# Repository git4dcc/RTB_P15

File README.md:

# RTB_P15

My homebrew P15 power board provides unmonitored power and is a stripped down version of the C11 power board. The main purpose of this card is to operate as a decoder tester/programmer via a USB connection to the PC. No external power supply is required as it can be powered via the USB and the optional isolated DC/DC converter.

<details>
<summary>See also</summary>

- [RTB_C10 - Master](/../../../../git4dcc/RTB_C10)
- [RTB_C11 - Power](/../../../../git4dcc/RTB_C11)
- [RTB_C12 - Booster](/../../../../git4dcc/RTB_C12)

</details>

<details>
<summary>User Guides</summary>

- User Guide - DE
- [User Guide - EN](https://rtb4dcc.de/rtb_user_guide_en/)

</details>

## Power Board features
- **passive**
  - no CPU on this board
- **DC/DC**
  - isolated DC/DC step up converter (5V->12V, 250mA)
  - (optional) external power connect (12V-16V, >1A)
- **Slots**
  - 1x Master slot
  - 1x Booster slot
  - 1x FDX extender (for development only)
- **Connectors**
  - terminal connector or (2.1mm / 2.5mm) barrel jack for external power
  - DCC connector

# Hardware
The PCB layout uses SMD footprints down to 0603 parts. Handsoldering is possible.
Further, the PCB has been optimized for automated assembly (BOM and Position files as CSV).

## PCB
- 2-layer PCB, FR4, 1.6mm
- CPU: none

# YouTube
See the (P15, C10, C12) used in the Decoder Tester use case.<br><br>

This project is intended for hobby use only and is distributed in accordance with the Apache License 2.0 agreement.

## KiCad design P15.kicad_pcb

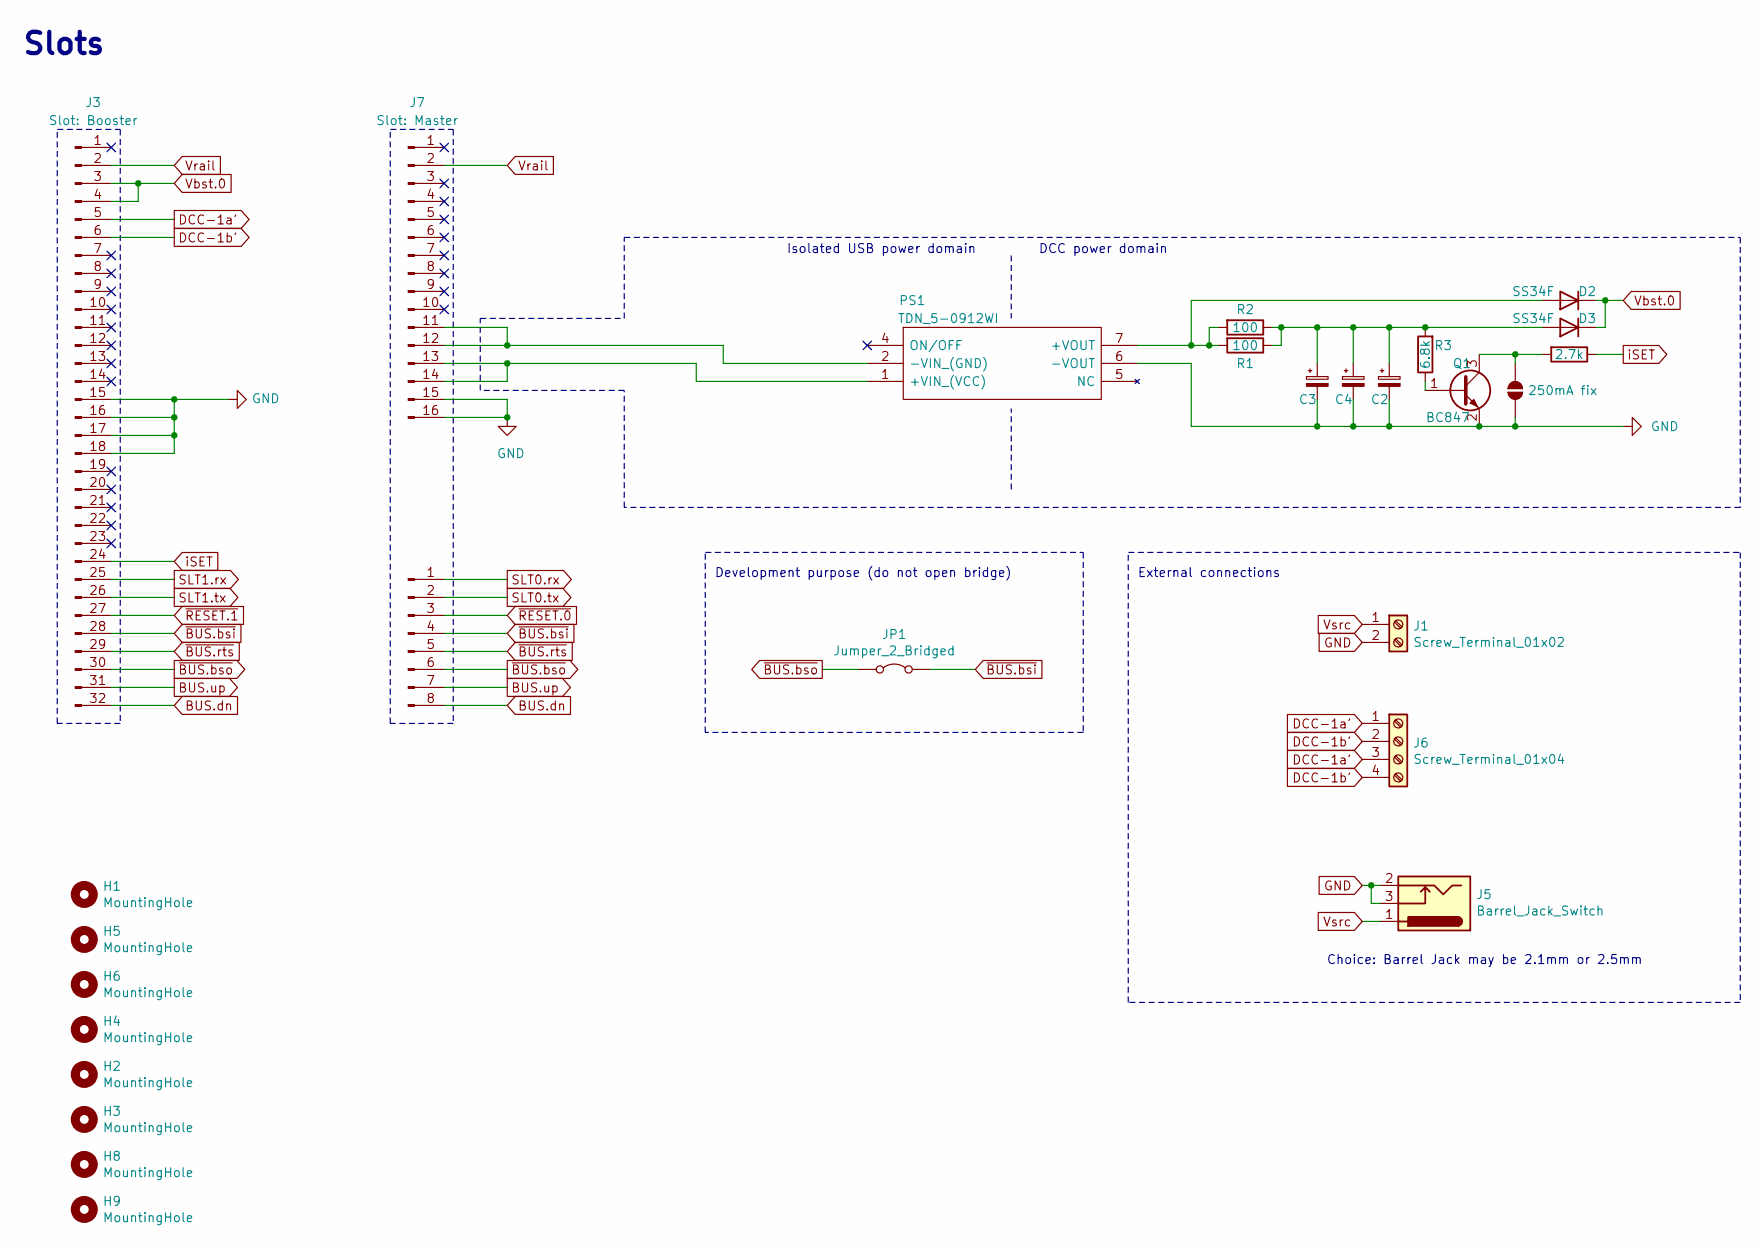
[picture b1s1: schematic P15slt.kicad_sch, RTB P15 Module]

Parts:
C2, C3, C4: 680u/20V; CP_Radial_D8.0mm_P3.50mm; Mouser 667-EEU-FR1E681L
D2, D3: SS34F; D_SOD-123F; LCSC Part # C60396
H1, H2, H3, H4, H5, H6, H8, H9: MountingHole; MountingHole_3.2mm_M3_ISO7380_Pad
J1: Screw_Terminal_01x02; 1725656
J3: Slot: Booster; PinSocket_1x32_P2.54mm_Vertical
J4: Slot-a1; PinSocket_1x08_P2.54mm_Vertical
J5: Barrel_Jack_Switch; BarrelJack_CLIFF_FC681465S_SMT_Horizontal; Mouser 163-0179-EX
J6: Screw_Terminal_01x04; 1725672
J7: Slot: Master; PinSocket_1x16_P2.54mm_Vertical
JP1: Jumper_2_Bridged; SolderJumper-2_P1.3mm_Bridged_RoundedPad1.0x1.5mm
JP2: 250mA fix; SolderJumper-2_P1.3mm_Open_Pad1.0x1.5mm
PS1: TDN_5-0912WI; TDN52412WI; Mouser 495-TDN5-0912WI
Q1: BC847; SOT-23; LCSC Part # C7420337
R1, R2: 100; R_1206_3216Metric; LCSC Part # C17901
R3: 6.8k; R_0603_1608Metric; LCSC Part # C23212
R4: 2.7k; R_0603_1608Metric; LCSC Part # C13167

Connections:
BUS.dn: J3.32, J4.8; also elsewhere on the board
BUS.up: J3.31, J4.7; also elsewhere on the board
DCC-1a': J3.5, J6.1, J6.3
DCC-1b': J3.6, J6.2, J6.4
GND: C2.2, C3.2, C4.2, J1.2, J3.15, J3.16, J3.17, J3.18, J5.2, J5.3, J7.15, J7.16, JP2.2 (B), PS1.6 (-VOUT), Q1.2 (E); also elsewhere on the board
unnamed: D2.2 (A), PS1.7 (+VOUT), R1.2, R2.2
unnamed: C2.1, C3.1, C4.1, D3.2 (A), R1.1, R2.1, R3.2
unnamed: J7.11, J7.12, PS1.2 (-VIN_(GND))
unnamed: J7.13, J7.14, PS1.1 (+VIN_(VCC))
unnamed: JP2.1 (A), Q1.3 (C), R4.2
unnamed: Q1.1 (B), R3.1
SLT0.rx: J4.1
SLT0.tx: J4.2
SLT1.rx: J3.25
SLT1.tx: J3.26
Vbst.0: D2.1 (K), D3.1 (K), J3.3, J3.4; also elsewhere on the board
Vrail: J3.2, J7.2; also elsewhere on the board
Vsrc: J1.1, J5.1; also elsewhere on the board
iSET: J3.24, R4.1
~BUS.bsi: J3.28, J4.4, JP1.2 (B); also elsewhere on the board
~BUS.bso: J3.30, J4.6, JP1.1 (A); also elsewhere on the board
~BUS.rts: J3.29, J4.5; also elsewhere on the board
~RESET.0: J4.3
~RESET.1: J3.27

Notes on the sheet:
Slots
Choice: Barrel Jack may be 2.1mm or 2.5mm
Isolated USB power domain
External connections
DCC power domain
Development purpose (do not open bridge)

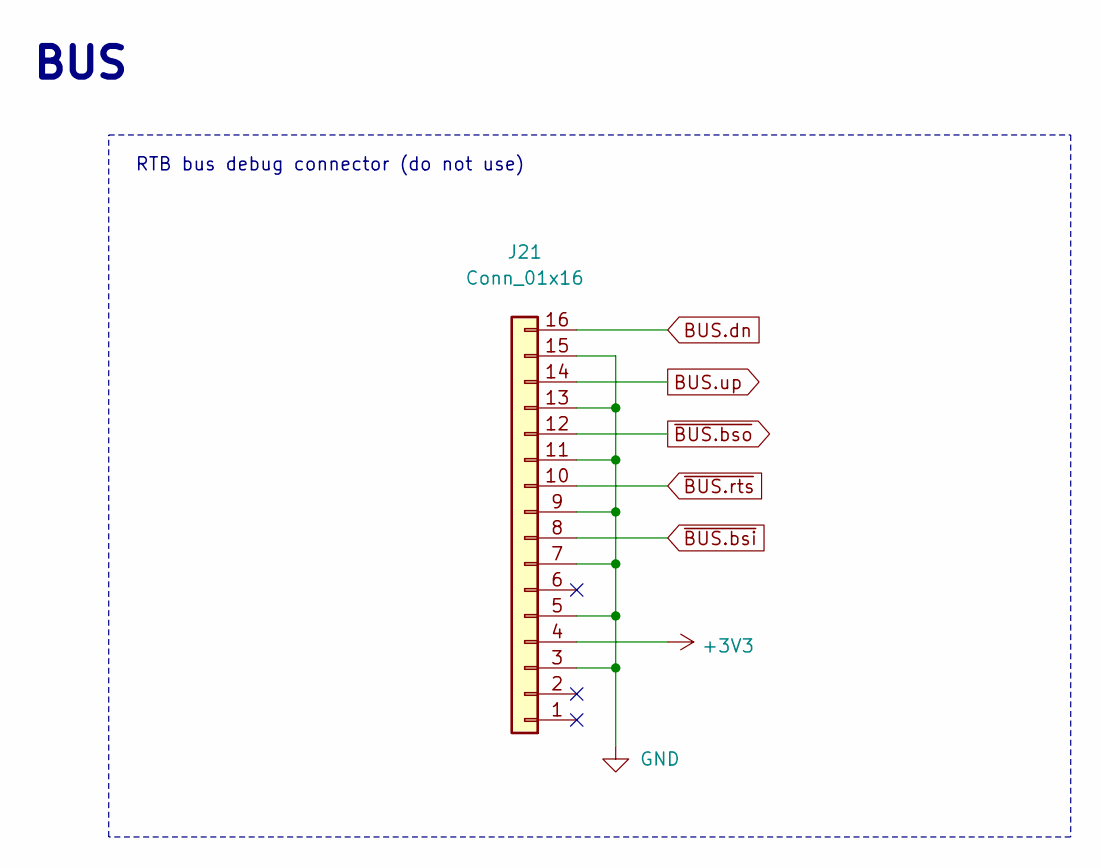
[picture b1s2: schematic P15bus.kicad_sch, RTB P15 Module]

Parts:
J21: Conn_01x16; PinHeader_2x08_P2.54mm_Vertical

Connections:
+3V3: J21.4
BUS.dn: J21.16; also elsewhere on the board
BUS.up: J21.14; also elsewhere on the board
GND: J21.3, J21.5, J21.7, J21.9, J21.11, J21.13, J21.15; also elsewhere on the board
~BUS.bsi: J21.8; also elsewhere on the board
~BUS.bso: J21.12; also elsewhere on the board
~BUS.rts: J21.10; also elsewhere on the board

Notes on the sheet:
RTB bus debug connector (do not use)
BUS

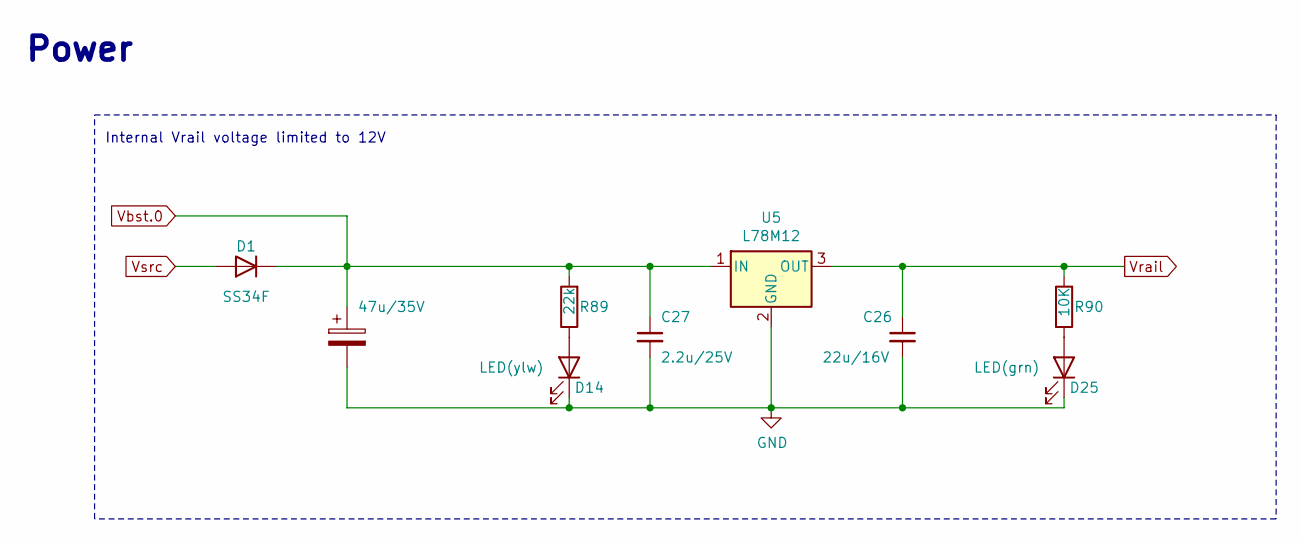
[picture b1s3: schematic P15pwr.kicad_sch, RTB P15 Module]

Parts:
C15: 47u/35V; CP_EIA-7343-43_Kemet-X; LCSC Part # C696814
C26: 22u/16V; C_1206_3216Metric; LCSC Part # C12891
C27: 2.2u/25V; C_1206_3216Metric; LCSC Part # C50254
D1: SS34F; D_SOD-123F; LCSC Part # C60396
D14: LED(ylw); LED_0603_1608Metric
D25: LED(grn); LED_0603_1608Metric
R89: 22k; R_0603_1608Metric; LCSC Part # C31850
R90: 10K; R_0603_1608Metric; LCSC Part # C25804
U5: L78M12; TO-252-2; LCSC Part # C22357875

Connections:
GND: C15.2, C26.2, C27.2, D14.1 (K), D25.1 (K), U5.2 (GND); also elsewhere on the board
unnamed: D14.2 (A), R89.1
unnamed: D25.2 (A), R90.1
Vbst.0: C15.1, C27.1, D1.1 (K), R89.2, U5.1 (IN); also elsewhere on the board
Vrail: C26.1, R90.2, U5.3 (OUT); also elsewhere on the board
Vsrc: D1.2 (A); also elsewhere on the board

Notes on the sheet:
Power
Internal Vrail voltage limited to 12V

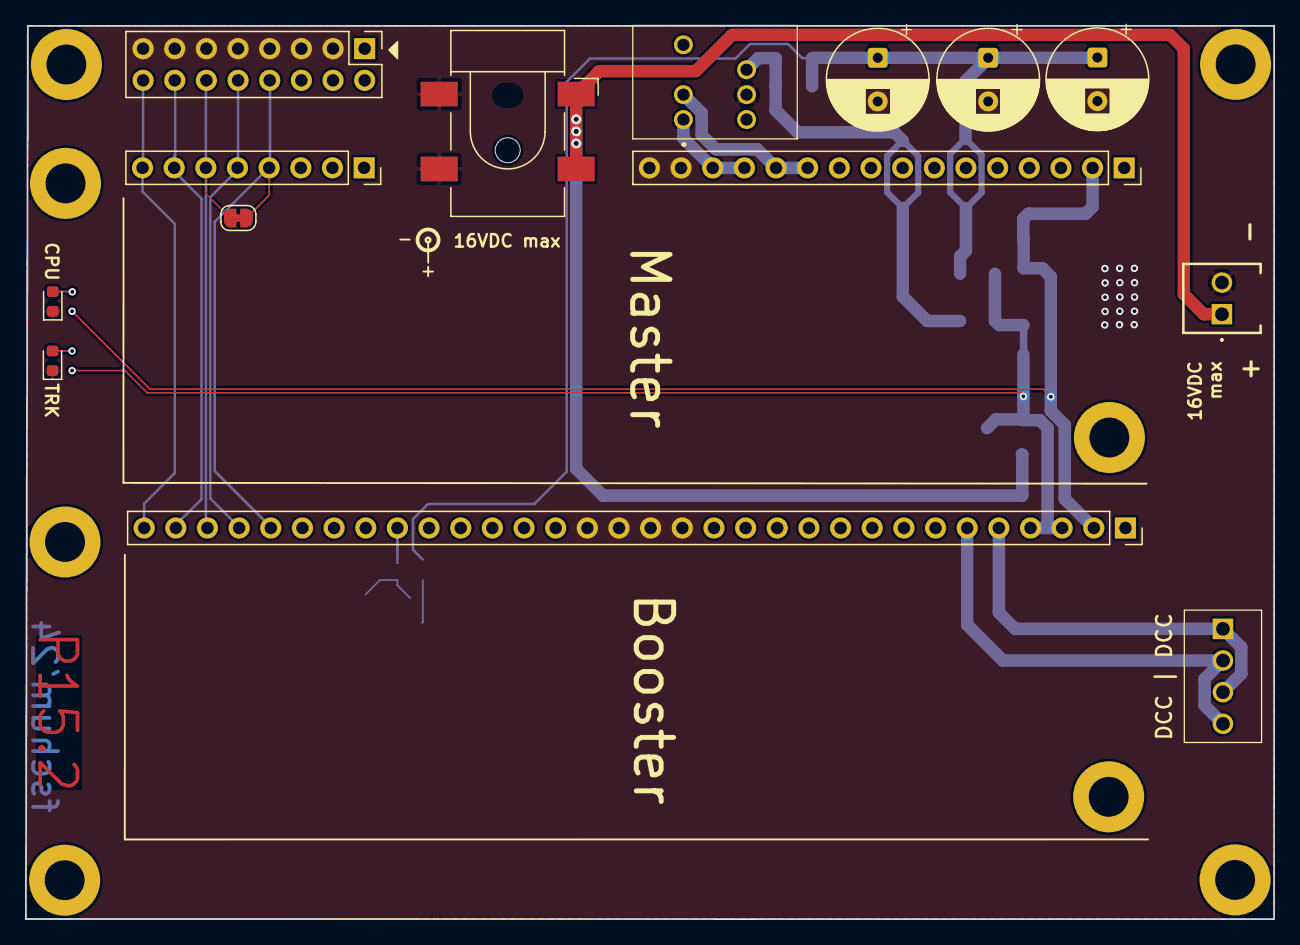
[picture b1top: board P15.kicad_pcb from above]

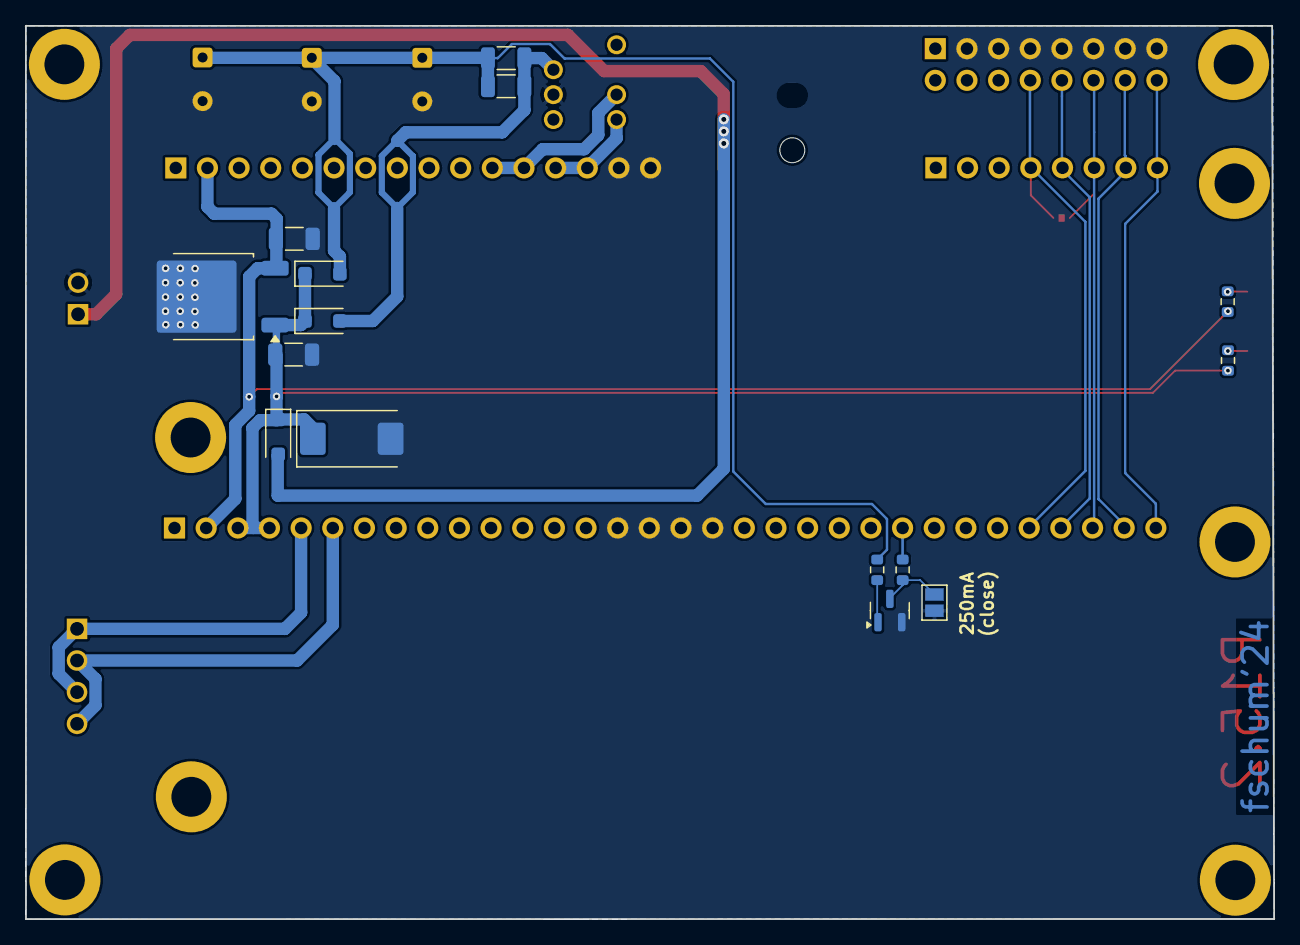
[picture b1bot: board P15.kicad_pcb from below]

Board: 2 copper layers, 100.2 x 71.7 mm, 37 parts (15 on the bottom side), 20 nets.

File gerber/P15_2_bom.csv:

Designator,Footprint,Quantity,Value,LCSC Part #
C15,CP_EIA-7343-43_Kemet-X,1,47u/35V,C696814
"C2, C3, C4",CP_Radial_D8.0mm_P3.50mm,3,680u/20V,
C26,1206,1,22u/16V,C12891
C27,1206,1,2.2u/25V,C50254
"D1, D2, D3",D_SOD-123F,3,SS34F,C60396
D14,0603,1,LED(ylw),
D25,0603,1,LED(grn),
"H1, H2, H3, H4, H5, H6, H8, H9",MountingHole_3.2mm_M3_ISO7380_Pad,8,MountingHole,
J1,1725656,1,Screw_Terminal_01x02,
J21,PinHeader_2x08_P2.54mm_Vertical,1,Conn_01x16,
J3,PinSocket_1x32_P2.54mm_Vertical,1,Slot: Booster,
J4,PinSocket_1x08_P2.54mm_Vertical,1,Slot-a1,
J5,BarrelJack_CLIFF_FC681465S_SMT_Horizontal,1,Barrel_Jack_Switch,
J6,1725672,1,Screw_Terminal_01x04,
J7,PinSocket_1x16_P2.54mm_Vertical,1,Slot: Master,
JP1,SolderJumper-2_P1.3mm_Bridged_RoundedPad1.0x1.5mm,1,Jumper_2_Bridged,
JP2,SolderJumper-2_P1.3mm_Open_Pad1.0x1.5mm,1,250mA fix,
PS1,TDN52412WI,1,TDN_5-0912WI,
Q1,SOT-23,1,BC847,C7420337
"R1, R2",1206,2,100,C17901
R3,0603,1,6.8k,C23212
R4,0603,1,2.7k,C13167
R89,0603,1,22k,C31850
R90,0603,1,10K,C25804
U5,TO-252-2,1,L78M12,C22357875

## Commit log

2025-09-04 mod: optimized for PCB assembly
2025-09-11 mod: corrected D2/D3 rotation
2025-09-25 upgrade to Kicad 9
2026-02-20 Change links to relative paths for RTB projects
    Updated links to relative paths in README.md.
2026-02-20 git mirror test

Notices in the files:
P15.kicad_pcb:
Licensed under the Apache License, Version 2
